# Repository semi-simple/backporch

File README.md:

# Backporch

Backporch is a board to connect many classic gaming consoles with widely
available and easily made cables with no components inside.  Backporch can then
be connected to PVMs (via HD15), Extron matrices, SCART TVs or
[OSSC](http://junkerhq.net/xrgb/index.php?title=OSSC) / [RetroTINK](https://www.retrotink.com/)
devices.

PVMs and Extron matrices can be connected with a simple VGA to BNC or VGA to
VGA cable. SCART TVs can be connected with a component-free Mini-DIN 8 to SCART
cable.

It is also possible to use Backporch to adapt any SCART cable into a TTL sync
output suitable for PVMs.

Backporch includes the necessary resistors, coupling caps and a sync stripper /
sync booster ([Renesas
EL1883](https://www.renesas.com/us/en/products/analog-products/audio-video/video-ics/video-sync-separators/el1883-sync-separator-horizontal-output)
or [Renesas
ISL59885](https://www.renesas.com/us/en/products/analog-products/audio-video/video-ics/video-sync-separators/isl59885-auto-adjusting-sync-separator-hd-and-sd-video))
for an excellent sync signal. Schematics [here](generated/schematics.pdf).

## Inputs

There are two inputs:

* The (mini) DIN 9 connector is suitable for consoles that output directly from
  a video amplifier to the back of the console.  Cables for such consoles
typically have impedence matching resistors as well as coupling capacitors.

* The (mini) DIN 8 connector (also usable as output) can be used to turn any
  existing SCART setup into a TTL sync setup suitable for PVMs. All one needs
is a simple passive SCART to (mini) DIN 8 cable such as the ones compatible
with the Framemeister XRGB mini.

It also can be used directly as input with a staight DIN 8 cable for consoles
that have retro mods, such as the NES RGB mod or some superguns.

## Outputs

There are two video outputs:

* The DE-15/HD-15 ("VGA") connector is suitable for PVMs (or the DE-15 input on
  the OSSC) and is best used with widely available HD15 to BNC cables. It will
output composite sync or separate H-SYNC and V-SYNC depending on the JP3
jumper.

* The (mini) DIN 8 connector (also usable as input) is suitable for SCART
  output using a widely available mini DIN 8 to SCART cable. This output can
also be used to connect directly to a Framemeister XRGB mini with a simple mini
DIN 8 cable.

Jumpers:

* JP1: Solder pad 1 (arrow) and 2 together (keep the 2-3 connection open)
* JP2: keep open for normal operation. If you never want to use the Mini DIN 8
  as an output, or if you're having sync issues, short it.
* JP3: Solder pad 2 and 3 together for an RGBS output with composite sync
  (CSYNC), or pad 1 (arrow) and 2 instead for a RGBHV output with separate
HSYNC and VSYNC.

## Supported consoles

### NES (Famicom) RGB mod

* If your mod uses the mini DIN 8 output, simply use a mini DIN 8 to mini DIN 8
  cable
* If your mod uses the multi-av output, solder a simple passive cable from the
  multi AV to mini DIN 8

### Sega Mega-Drive / Genesis 2

* Use a simple mini DIN 9 to mini DIN 9 cable.

Sega 32X cables work well, but all pins need to be connected. Some
high quality, proper 32X cables don't have PIN 2 (5V) connected. Most "cheap"
cables on Ebay have all pins connected. Some bad cables don't have ground
connected.

(You can use cables without PIN 2 if you don't solder U1 and change JP1)

### Sega Mega-Drive / Genesis 1

* There are many model 1 to model 2 adapters available

### Super Nintendo / Super Famicom

* If your Super Nintendo is modded with an RGB bypass mod, you can build a
  simple cable from MultiAV to mini-din 8.  Wire sync (Pin 3) from either
composite or Luma (better!). This will work for either PAL or NTSC consoles! If
you have CSYNC wired, you can use that instead, but ideally configure your RGB
bypass board to output 75 Ohm CSYNC.

* Unmodded Super Nintendo are not supported at this time as they require
  coupling capacitors (things will work without them, but this setup might draw
excessive current from the video amplifiers).

Of course, if you already have a SCART cable for your Super Nintendo, you can
still use Backporch to [restore TTL sync and plug it to a PVM](#anything-else).

### PC Engine/ TurboGrafx-16

Either with Terraonion's SSDS3, Insurrection Industries' Spark Plug or the db
GrafxBooster TTP:

* Same as [Sega Mega-Drive / Genesis 2](#sega-mega-drive--genesis-2).

### Neo Geo AES

* Build a simple passive cable from the Neo Geo DIN8 to standard Mini DIN 8

### Neo Geo MVS

* If you use the [Minigun
  Supergun](https://www.arcade-projects.com/threads/minigun-supergun-an-open-source-supergun.9408/)
or the [HAS](https://homearcadesystem.wordpress.com/about/), you can simply use
a Mini DIN8 to Mini DIN8 cable between the Supergun and Backporch.

### Anything else

If you already have a SCART cable for your device and all you need is a sync
stripper / booster to connect to a PVM or an Extron matrix, you can use any
SCART to mini DIN 8 cable, such as the ones used for the Framemeister XRGB
mini.

## Getting good cables

Ideally, proper analog video transmission should happens over 75 Ohm coaxial
cables.  [Proper impedence
matching](https://en.wikipedia.org/wiki/Impedance_matching#Transmission_lines)
requires a 75 Ohm resistor at the source and a 75 Ohm resistor at the
destination. This is why many retro-gaming cables that have resistors meant for
the source inside the SCART (near the destination) are not proper. At the
frequencies used in classic gaming console signals, this only really matters
for very long cables though.

You should strive to use high quality shielded cables to Backporch and keep
them short. If only one of those properties holds true, you should still be
fine. Properly shielded 75 Ohm cables used from Backporch's outputs can be
long.

Use [this issue](https://github.com/semi-simple/backporch/issues/1) for a
discussion of where to source good cables.

## Ordering the board

You can order the board directly from Oshpark
[here](https://oshpark.com/shared_projects/adF28fFL) or download the Gerber
files from them and send those to your favorite manufacturer.

You can order the needed components by using this
[BOM file](generated/backporch_bom.csv). If you order from Digi-Key, you can
simply upload this file to them.

## FAQ

* What does the name mean?

It's a small deck at the back of your console (back porch). It's also a
reference to the blanking interval after the sync pulse in video signals.

* Do I need all those components?

Maybe not. For many inputs, if you know what you're doing, you can remove
all components related to sync stripping and use JP1 to send sync directly to
HSYNC on the DE-15 port. For THS737X mods ("RGB bypass"), coupling capacitors
are not needed. Remove the big electrolytic capacitors and bridge the footprint
of the small ones.

* There is "noise" when connecting to an OSSC via DE-15. What gives?

The DE-15 input (AV3) on the OSSC does not have a proper low-pass filter. You can
use the SCART input instead, or you can route the RGB lines to AV2 instead (via
BNC/RCA adaptors and VGA/BNC breakout cables) and use the "AV3 use alt. RGB"
option on the OSSC.

* I like the Renesas ISL59885 chip better. Could I use it instead?

You're in luck: it works as a drop-in replacement for U1. Just keep R2
unpopulated and replace C2 with a 56nF X7R grade capacitor.

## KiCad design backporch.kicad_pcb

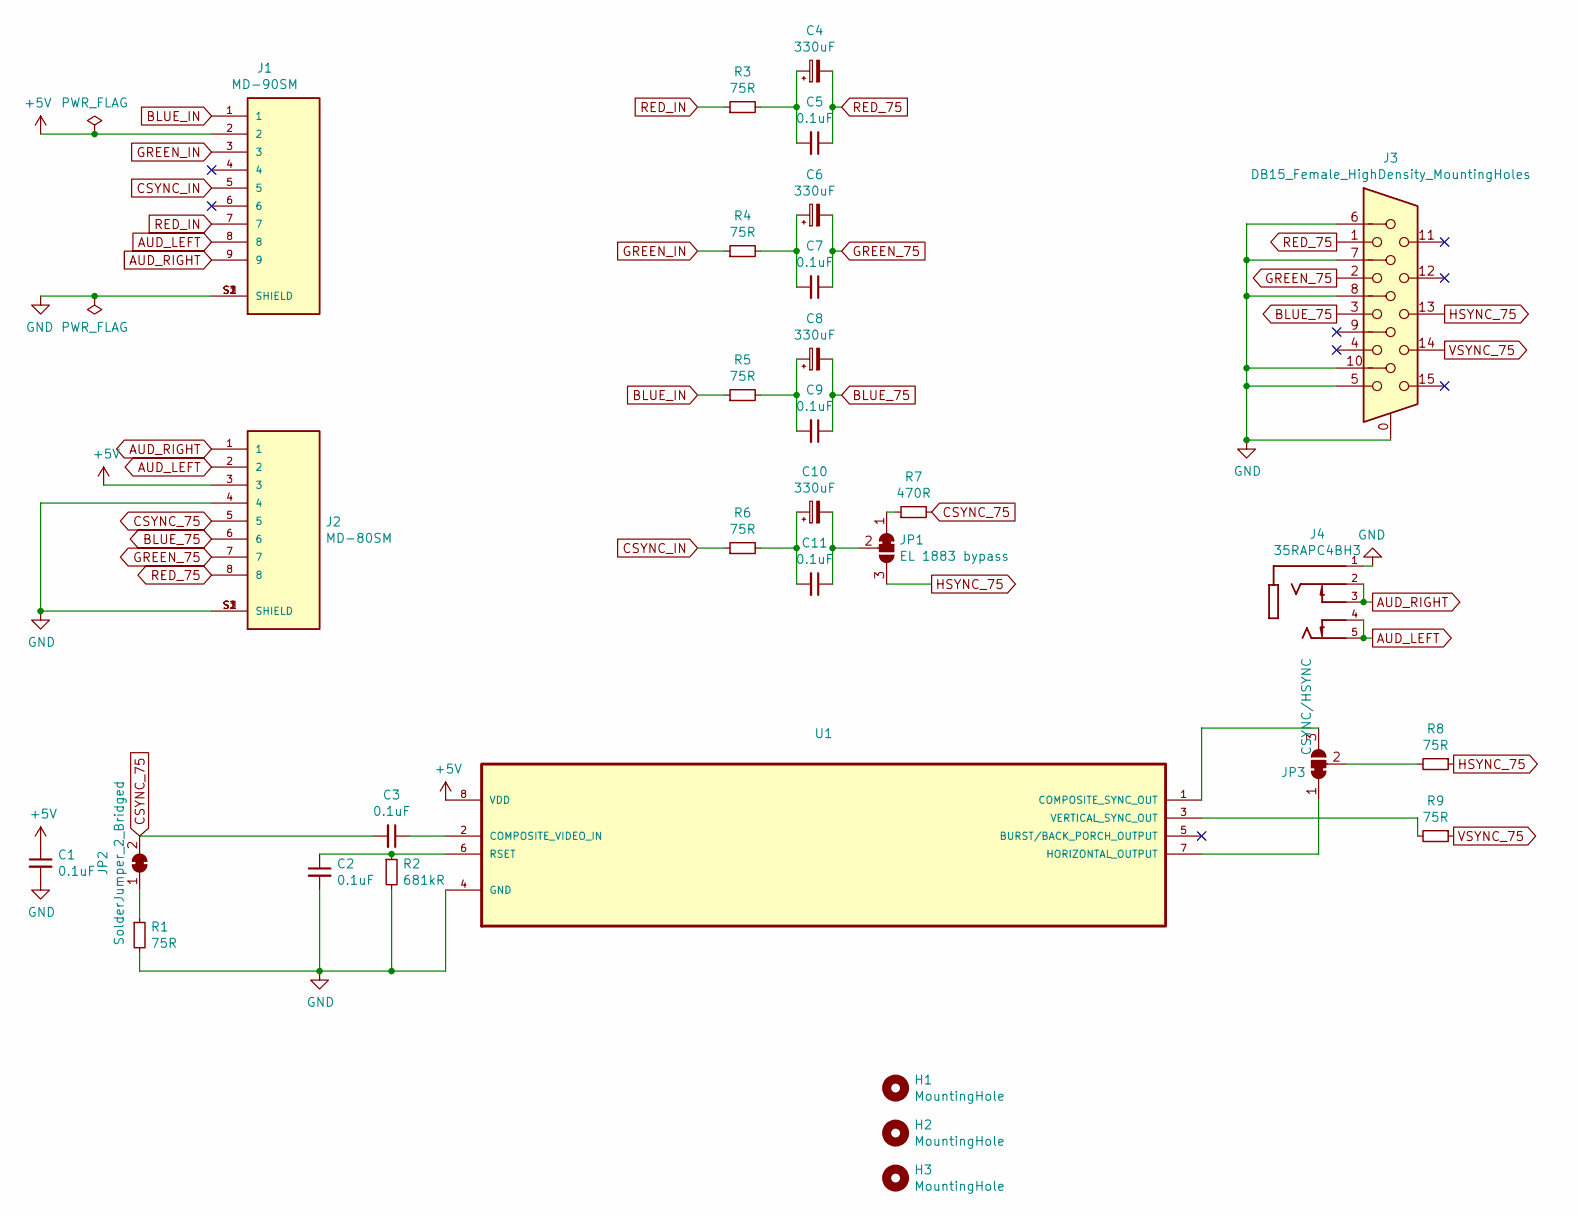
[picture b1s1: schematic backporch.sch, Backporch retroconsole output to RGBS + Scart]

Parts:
C1, C2, C3, C5, C7, C9, C11: 0.1uF; C_1206_3216Metric_Pad1.42x1.75mm_HandSolder; Digi-key part number 399-1259-1-ND
C4, C6, C8, C10: 330uF; CP_Radial_D6.3mm_P2.50mm; Digi-key part number 493-1268-ND
H1, H2, H3: MountingHole; MountingHole_2.2mm_M2_ISO7380_Pad
J1: MD-90SM; CUI_MD-90SM; PARTREV 1.05; Digi-key part number CP-2290-ND
J2: MD-80SM; CUI_MD-80SM; PARTREV 1.05; Digi-key part number CP-2280-ND
J3: DB15_Female_HighDensity_MountingHoles; VGA_CONN; Manufacturer Part Number AHDF15A-KG-TAXB; Digi-key part number AE11024-ND
J4: 35RAPC4BH3; SWITCHCRAFT_35RAPC4BH3; PARTREV J; Digi-key part number SC1464-ND
JP1: EL 1883 bypass; SolderJumper-3_P1.3mm_Open_Pad1.0x1.5mm
JP2: SolderJumper_2_Bridged; SolderJumper-2_P1.3mm_Open_Pad1.0x1.5mm
JP3: CSYNC/HSYNC; SolderJumper-3_P1.3mm_Open_Pad1.0x1.5mm
R1, R3, R4, R5, R6, R8, R9: 75R; R_1206_3216Metric_Pad1.42x1.75mm_HandSolder; Digi-key part number P75.0FCT-ND
R2: 681kR; R_1206_3216Metric_Pad1.42x1.75mm_HandSolder; Digi-key part number P681KFCT-ND
R7: 470R; R_1206_3216Metric_Pad1.42x1.75mm_HandSolder; Digi-key part number P470FCT-ND
U1: EL1883ISZ; SOIC127P600X175-8N; MPN EL1883ISZ; Digi-key part number EL1883ISZ-ND

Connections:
+5V: C1.1, J1.2, J2.3, U1.8 (VDD)
AUD_LEFT: J1.8, J2.2, J4.4, J4.5
AUD_RIGHT: J1.9, J2.1, J4.2, J4.3
BLUE_75: C8.2, C9.1, J2.6, J3.3
BLUE_IN: J1.1, R5.1
CSYNC_75: C3.2, J2.5, JP2.2 (B), R7.2
CSYNC_IN: J1.5, R6.1
GND: C1.2, C2.2, J1.S1 (SHIELD), J1.S2 (SHIELD), J1.S3 (SHIELD), J2.4, J2.S1 (SHIELD), J2.S2 (SHIELD), J2.S3 (SHIELD), J3.0, J3.5, J3.6, J3.7, J3.8, J3.10, J4.1, R1.2, R2.2, U1.4 (GND)
GREEN_75: C6.2, C7.1, J2.7, J3.2
GREEN_IN: J1.3, R4.1
HSYNC_75: J3.13, JP1.3 (B), R8.1
unnamed: C2.1, R2.1, U1.6 (RSET)
unnamed: C3.1, U1.2 (COMPOSITE_VIDEO_IN)
unnamed: C4.1, C5.2, R3.2
unnamed: C6.1, C7.2, R4.2
unnamed: C8.1, C9.2, R5.2
unnamed: C10.1, C11.2, R6.2
unnamed: C10.2, C11.1, JP1.2 (C)
unnamed: JP1.1 (A), R7.1
unnamed: JP2.1 (A), R1.1
unnamed: JP3.1 (A), U1.7 (HORIZONTAL_OUTPUT)
unnamed: JP3.2 (C), R8.2
unnamed: JP3.3 (B), U1.1 (COMPOSITE_SYNC_OUT)
unnamed: R9.2, U1.3 (VERTICAL_SYNC_OUT)
RED_75: C4.2, C5.1, J2.8, J3.1
RED_IN: J1.7, R3.1
VSYNC_75: J3.14, R9.1

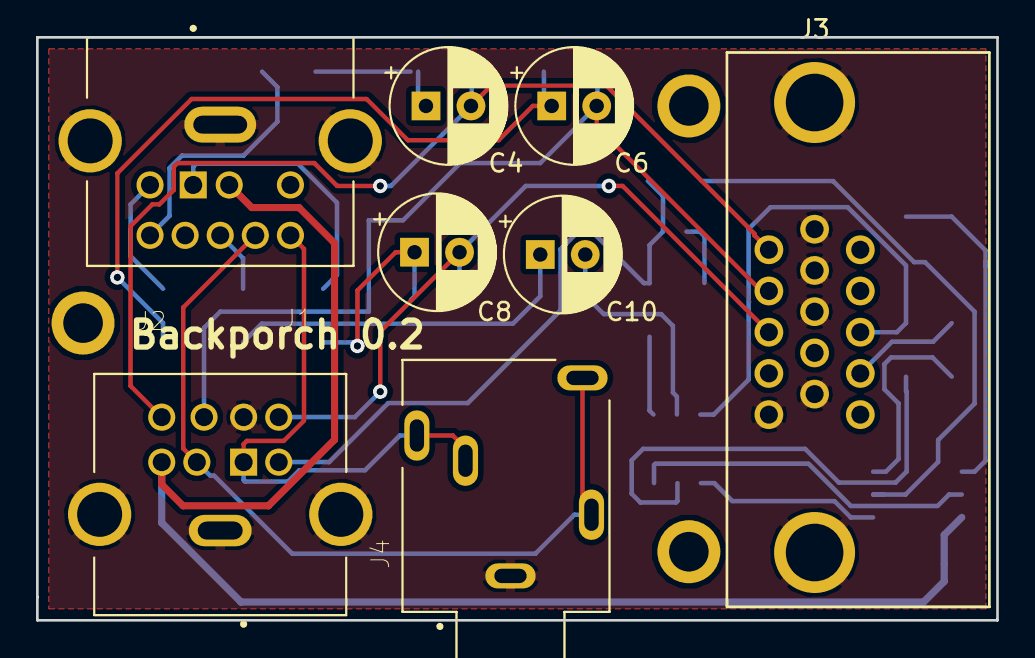
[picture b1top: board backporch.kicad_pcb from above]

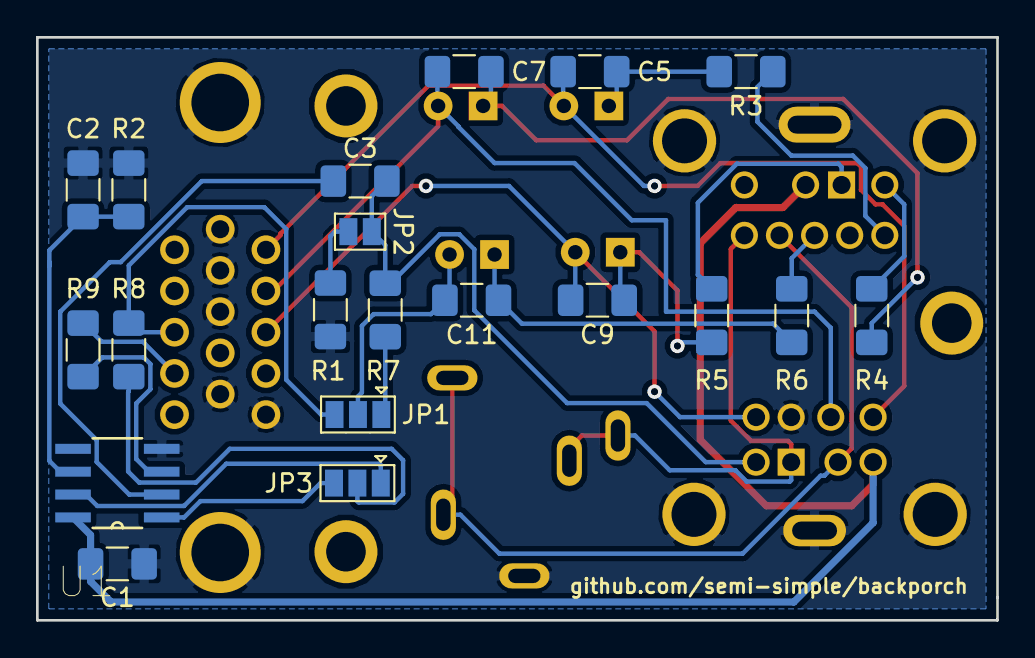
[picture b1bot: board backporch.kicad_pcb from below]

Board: 2 copper layers, 53.3 x 32.4 mm, 31 parts (20 on the bottom side), 27 nets.

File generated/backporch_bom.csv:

Component,Part,Description,References,Value,Quantity Per PCB,Digi-key part number
1,C_Small,"Unpolarized capacitor, small symbol",C1 C2 C3 C5 C7 C9 C11,0.1uF,7,399-1259-1-ND
2,CP_Small,"Polarized capacitor, small symbol",C4 C6 C8 C10,330uF,4,493-1268-ND
3,35RAPC4BH3,,J4,35RAPC4BH3,1,SC1464-ND
4,DB15_Female_HighDensity_MountingHoles,"15-pin female D-SUB connector, High density (3 columns), Triple Row, Generic, VGA-connector, Mounting Hole",J3,DB15_Female_HighDensity_MountingHoles,1,AE11024-ND
5,MD-80SM,,J2,MD-80SM,1,CP-2280-ND
6,MD-90SM,,J1,MD-90SM,1,CP-2290-ND
7,R_Small,"Resistor, small symbol",R1 R3 R4 R5 R6 R8 R9,75R,7,P75.0FCT-ND
8,R_Small,"Resistor, small symbol",R7,470R,1,P470FCT-ND
9,R_Small,"Resistor, small symbol",R2,681kR,1,P681KFCT-ND
10,EL1883ISZ,,U1,EL1883ISZ,1,EL1883ISZ-ND

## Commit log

2021-02-10 README: various updates
2021-02-10 Add mounting holes
2021-02-10 Schematics: add PDF file for convenience
2021-02-12 Add BOM configuration and file
2021-02-24 Backporch 0.2: Swap pin 3 and 5 on mini-DIN 8
    For some reason, CUI devices labeling of their pins for their mini-DIN 8
    is different from everybody else's and also different from their other
    mini DIN connectors.
    This fixes a major issue where +5V and sync were swapped on the
    mini-DIN 8 connector.
2021-02-25 Update DE-15/VGA connector footprint
    KiCad's DE-15 footprint is not correct for right angle connectors,
    making it difficult to fit standard connectors.
    Use VGA_CONN footprint from the OSSC project at
    https://github.com/marqs85/ossc_pcb instead as a workaround.
2021-02-25 README.md: add note about mini DIN8 input
    Add clarification that Backporch can be used like a Sync Slayer or
    Sync Strike with a simple passive cable.
2021-02-25 README: add picture of assembled board
2021-02-25 PCB: add GitHub URL to silkscreen
2021-02-28 PCB: add space between signal traces
2021-02-28 README: offer ISL59885 as an alternative U1
    At the suggestion of Raph_friend, document ISL59885 as valid alternative
    for U1 explicitly.
2021-03-02 README: add some info on sourcing good cables.
2021-03-21 Symbols: add external symbols to project
2021-03-21 Footprints: add external footprints to project
2021-03-21 README: change picture to that of Backporch 0.2
